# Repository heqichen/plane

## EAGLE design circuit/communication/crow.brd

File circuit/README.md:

using eagle 7.0

#ruels
1. resistor
R-US_0207/10(R-US)

2. smd resistor
R-US M0805

3. Jumper
PINHD-<num>x<num>

4. Capasitor
cpol-usud-5X5,8

5. SMA
view crow

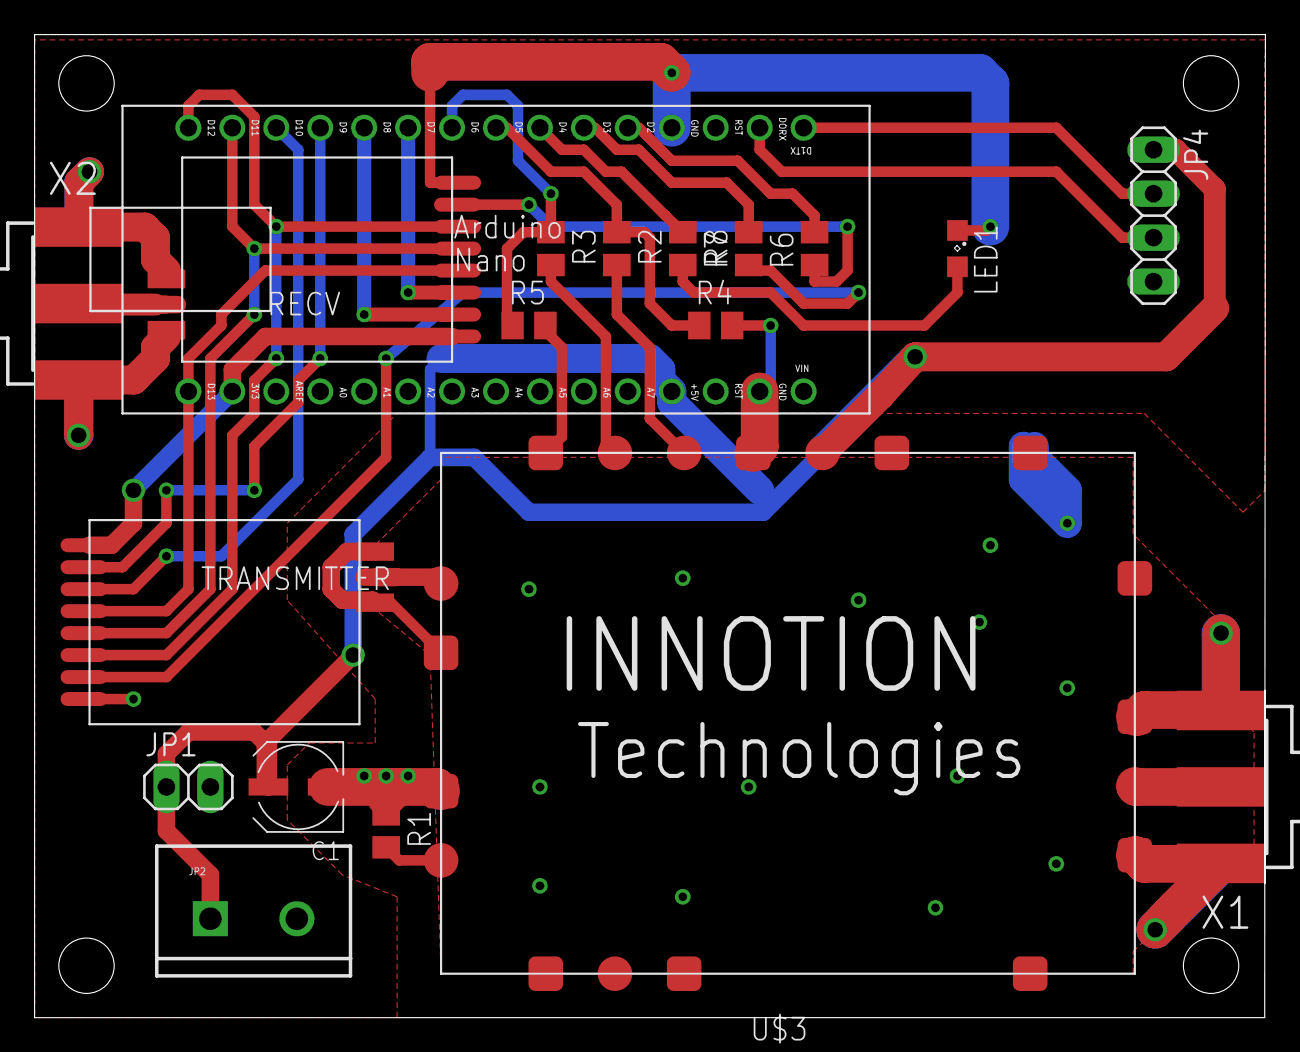
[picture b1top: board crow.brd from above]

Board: 2 copper layers, 71.1 x 56.8 mm, 19 parts (0 on the bottom side), 26 nets.

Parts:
C1: UD-5X5,8_NICHICON
JP1: 1X02
JP2: M025MM; SCREWTERMINAL-5MM-2
JP4: 1X04
LED1: SML0805
PCB1: ARDUINO_NANO_EXT; ARDUINO_NANO
R1: 50; M0805
R2, R3, R5, R6, R7, R8: 1k; M0805
R4: 10k; M0805
RECV: NRF24L01-AS01-ML01IPX; AS01-ML01IPX
TRANSMITTER: NRF24L01-AS01-ML01IPX; AS01-ML01IPX
U$3: 2.5W-TDD
X1, X2: SMA-142-0701-801/806; J502-ND-142-0701-801/806

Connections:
3V3: PCB1.3V3, RECV.3V3, TRANSMITTER.3V3
5V: C1.+, JP1.1, JP2.1, JP4.1, PCB1.5V, U$3.VPA
D2: PCB1.D2, R6.2
D3: PCB1.D3, R7.2
D5: PCB1.D5, R2.1, R4.1
D6: PCB1.D6, R3.1, R5.1
D7: PCB1.D7, RECV.CSN
D8: PCB1.D8, RECV.CE
D9: PCB1.D9, TRANSMITTER.CE
D10: PCB1.D10, TRANSMITTER.CSN
GND: C1.-, JP1.2, JP2.2, JP4.4, LED1.C, PCB1.GND, PCB1.GND., R1.1, R4.2, R5.2, RECV.GND, RECV.GND-ANT1, RECV.GND-ANT2, TRANSMITTER.GND, TRANSMITTER.GND-ANT1, TRANSMITTER.GND-ANT2, U$3.GND1, U$3.GND1-ANT, U$3.GND2, U$3.GND2-ANT, U$3.GND3, U$3.GND4, U$3.GND5, U$3.GND6, U$3.GND-RFIN, U$3.GND-RFOUT, U$3.GND-RX, U$3.GND-TX, X1.G@1, X1.G@2, X1.G@3, X1.G@4, X2.G@1, X2.G@2, X2.G@3, X2.G@4
MISO: PCB1.D12, RECV.MISO, TRANSMITTER.MISO
MOSI: PCB1.D11, RECV.MOSI, TRANSMITTER.MOSI
unnamed: R1.2, U$3.RFIN
unnamed: U$3.ANT, X1.1
unnamed: R7.1, TRANSMITTER.IRQ
unnamed: RECV.ANT, X2.1
unnamed: TRANSMITTER.ANT, U$3.RFOUT
unnamed: R6.1, RECV.IRQ
unnamed: PCB1.D4, R8.1
unnamed: LED1.A, R8.2
RX: JP4.3, PCB1.RX1
RXEN: R3.2, U$3.RX
SCK: PCB1.D13, RECV.SCK, TRANSMITTER.SCK
TX: JP4.2, PCB1.TX1
TXEN: R2.2, U$3.TX

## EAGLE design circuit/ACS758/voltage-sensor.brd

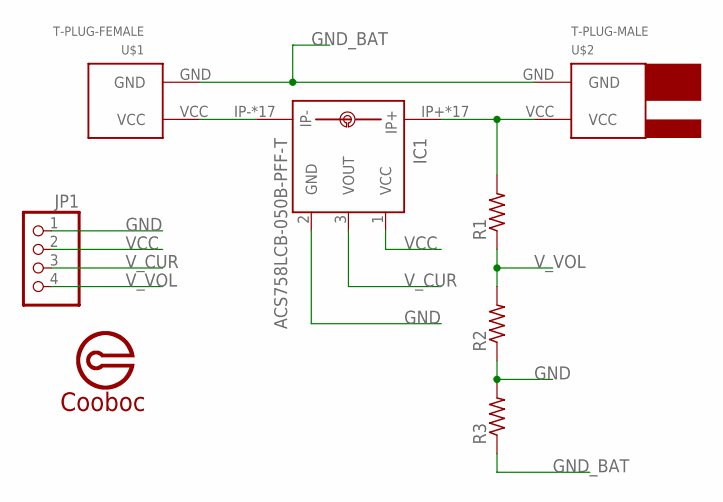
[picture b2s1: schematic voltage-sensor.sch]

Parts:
IC1: ACS758LCB-050B-PFF-T; CB-PFF
JP1: PINHD-1X4; 1X04
R1, R2: R-US_M0805; M0805
R3: R-US_0207/10; 0207/10
U$1: T-PLUG-FEMALE; T-FEMALE
U$2: T-PLUG-MALE; T-MALE
U$3: COOBOC

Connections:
GND: IC1.2 (GND), JP1.1, R2.1, R3.2; also elsewhere on the board
GND_BAT: R3.1, U$1.GND, U$2.GND
unnamed: IC1.IP-, IC1.IP-@2 (IP-), IC1.IP-@3 (IP-), IC1.IP-@4 (IP-), IC1.IP-@5 (IP-), IC1.IP-@6 (IP-), IC1.IP-@7 (IP-), IC1.IP-@8 (IP-), IC1.IP-@9 (IP-), IC1.IP-@10 (IP-), IC1.IP-@11 (IP-), IC1.IP-@12 (IP-), IC1.IP-@13 (IP-), IC1.IP-@14 (IP-), IC1.IP-@15 (IP-), IC1.IP-@16 (IP-), IC1.IP-@17 (IP-), U$1.VCC
VBAT: IC1.IP+, IC1.IP+@2 (IP+), IC1.IP+@3 (IP+), IC1.IP+@4 (IP+), IC1.IP+@5 (IP+), IC1.IP+@6 (IP+), IC1.IP+@7 (IP+), IC1.IP+@8 (IP+), IC1.IP+@9 (IP+), IC1.IP+@10 (IP+), IC1.IP+@11 (IP+), IC1.IP+@12 (IP+), IC1.IP+@13 (IP+), IC1.IP+@14 (IP+), IC1.IP+@15 (IP+), IC1.IP+@16 (IP+), IC1.IP+@17 (IP+), R1.2, U$2.VCC
VCC: IC1.1 (VCC), JP1.2; also elsewhere on the board
V_CUR: IC1.3 (VOUT), JP1.3
V_VOL: JP1.4, R1.1, R2.2

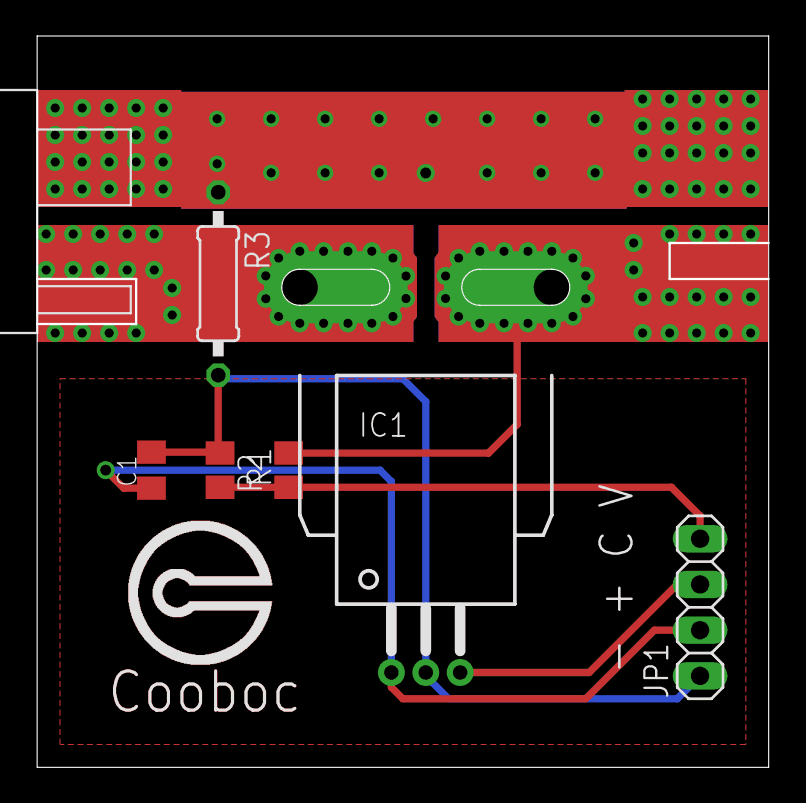
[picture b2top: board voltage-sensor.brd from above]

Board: 2 copper layers, 40.6 x 40.5 mm, 9 parts (1 on the bottom side), 7 nets.

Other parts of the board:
C1: C0805K

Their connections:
GND: C1.2; also elsewhere on the board
VCC: C1.1; also elsewhere on the board

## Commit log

2015-01-28 test arduino is good
2015-01-28 add nrf24l01 test
2015-02-16 test nrf24l01 no_ack success
2015-02-17 now can send data using nRF24l01 without ack
2015-02-17 add comment
2015-02-17 transmitter using nRF24l01 finished
2015-02-17 now can transmit data using nRF24l01
2015-02-18 change buadrate to 9600
2015-02-19 add mavlink protocol
2015-02-19 add useful nodes
2015-02-19 now can control the flight and read data from flightGear
2015-02-19 update protocol to json
2015-02-19 add gitignore file
2015-02-19 update gitignore
2015-02-19 now can read joystick value
2015-02-19 now can control flightgear with joystick
2015-02-19 add hexafsg
2015-02-20 now can show flight attitude on hexsfg
2015-02-20 update flightgear start command
2015-02-20 add makefile
2015-02-20 now can get radio
2015-02-20 add device framework
2015-02-20 add setup env script
2015-02-21 now can use radio
2015-02-21 add imu class
2015-02-21 add bmx055 driver without implementation
2015-02-21 now can start bmx055
2015-02-21 now can wakeup chicken
2015-02-21 remove chicken binary from repo
2015-02-21 now can reset acc and gyro
2015-02-21 now can read gyro data
2015-02-21 now can read acc
2015-02-21 now can running imu thread
2015-02-21 can get data from imu
2015-02-21 can send imu data via mavlink
2015-02-21 add mavlink
2015-02-22 raise update rate
2015-02-22 add auto start script
2015-02-22 add serial port -> mavlink -> flightgear test code
2015-02-23 add buzz ArduPPM
2015-02-23 pwm signal generater box finished
2015-02-23 test mavnlink generator box good
2015-02-23 now servo board can read pwm rc signal
2015-02-23 format code
2015-02-23 now can output pwm signal using rc, using Arduin Servo Library
2015-02-24 change output to simple servo output
2015-02-24 servo board can read mavlink override rc signal
2015-02-24 can send raw rc channel via serial1
2015-02-24 git remove deleted file
2015-02-24 send mavlink and write pwm in a certin routine
2015-02-24 add utp script
2015-02-24 change configuration buadrate
2015-02-24 add servo_controller
2015-02-24 reset uart to serial radio
2015-02-24 add SerialServoDriver
2015-02-24 now can read one rc channel from serial
2015-02-25 can read rc signal in chicken now
2015-02-25 now can send rc signal in driver
2015-02-25 reduce delay
2015-02-25 dummy commit
2015-02-25 nwo can override rc channel
2015-02-25 move global variable to imu member
2015-02-25 test lantcy on mega
2015-02-25 reduce servo control delay
2015-02-26 reduce servo control delay on bbb
2015-02-26 add 38400 transmitter
2015-02-26 correct folder name from dtx-38400 to dtx24-38400
2015-02-26 rename nood to node
2015-02-26 add gps test data
2015-02-27 now can read one channel data from ads7828
2015-02-27 now can read aoa and side slip
2015-02-27 add gpio library from https://github.com/mkaczanowski/BeagleBoneBlack-GPIO
2015-02-27 add files for gpio
2015-02-27 add beeper_driver files
2015-02-27 add beeper driver
2015-02-27 add beeper device
2015-02-27 beeper finished
2015-02-28 update ntp server
2015-02-28 now can read magnetometer
2015-02-28 bugfix: correct magnetometer data
2015-03-01 change beeper pin to P9_42
2015-03-01 update gpiomanager and add ultrasonic driver
2015-03-01 add ultrasonic test code on arduino
2015-03-01 bug: epoll do not work
2015-03-01 ir proximity sensor done
2015-03-02 add uav photo
2015-03-03 add test code for nrf24l01
2015-03-03 add crow communication module folder
2015-03-03 change csn pin
2015-03-03 change wide band variablewq
2015-03-03 change pvar to 24l01plus
2015-03-03 change payload size
2015-03-03 change ackpayloadAvailabe
2015-03-03 change is dynamic paload enable
2015-03-03 change ackpayloadlenght
2015-03-03 change last address set on pipe0
2015-03-03 change spi and pin
2015-03-03 update begin functionwq
2015-03-03 change writeRegister
2015-03-03 change readRegister
2015-03-03 move setPALevel
2015-03-03 update pa related code
2015-03-03 update setDataRate
2015-03-03 update setCRCLength
2015-03-03 update setDynamicPayloads
2015-03-03 update toggleFetature
2015-03-03 update flush related functions
2015-03-03 now can send and receive in full duplex
2015-03-03 complete test code for full duplex commnucatioin module
2015-03-03 add altitude fusion
2015-03-03 corrent altitude fusion to attitude indicator
2015-03-03 add virtualImu
2015-03-03 add radio fetch thread
2015-03-04 move arduino test program to arduino folder
2015-03-04 add ACS756 application image
2015-03-04 cam read attitude from flightgear and send to chicken
2015-03-04 now can read attitude from radio mavlink massage
2015-03-04 now can output virutal imu data
2015-03-04 add adi
2015-03-04 adi finished
2015-03-04 test adi
2015-03-04 output data in rad
2015-03-05 add interval thread
2015-03-05 now can decide flight status
2015-03-05 add pid files
2015-03-05 add average filter
2015-03-05 now can control elevator
2015-03-05 add servo control mode
2015-03-05 add I in pid
2015-03-05 add attitude navigator
2015-03-05 now can switch navigator
2015-03-05 add Navigator interface
2015-03-05 change manully navigator to navigator interface
2015-03-05 change all navitgator follow INavigator interface
2015-03-06 can stablize static target attitude
2015-03-06 now can stablize roll
2015-03-06 now can change attitude target in attitude navigator
2015-03-06 remove Attitude , duplicated with ImuAttitude
2015-03-06 add rudder control when bank angle
2015-03-06 now can control pitch and roll
2015-03-06 now can stablize yaw using rudder
2015-03-06 update pid parameter
2015-03-06 stalizer finished
2015-03-07 add cad file
2015-03-07 bulkhead with side holder
2015-03-07 add holes on fuselage
2015-03-07 add connector with button panel
2015-03-07 add connect between bulkhead and bottom
2015-03-07 add connector with top
2015-03-07 remove temp file
2015-03-08 bugfix: resoleve top cover conflict
2015-03-08 fuselage finished
2015-03-08 add connecting hole
2015-03-09 add cut file of 20150208
2015-03-09 vw side connect finished
2015-03-09 add hole on bulkhead
2015-03-09 add center holes on bulkhead
2015-03-09 add bottom panel
2015-03-09 change to 2mm
2015-03-09 cut this version and fix some bug
2015-03-09 add connect on top
2015-03-09 bugfix, filber tube is 16mm
2015-03-09 move hole to correct position
2015-03-09 add circuit folder
2015-03-09 add acs758
2015-03-09 update gitignore file add eagle backup file
2015-03-10 add male t plug
2015-03-10 add female t plug
2015-03-10 add some library
2015-03-10 add resistor rules
2015-03-10 update design rules
2015-03-10 sch done
2015-03-10 add eagle backup files to gitignore
2015-03-10 voltage and current sensor done
2015-03-10 layout done
2015-03-10 add capicator on asc758
2015-03-10 add arduino library from element14
2015-03-10 add top cover
2015-03-10 add back top cover
2015-03-10 add connection to kt side board
2015-03-10 add hole on back top board
2015-03-10 rm librecad backup file
2015-03-10 i don't know where changed...
2015-03-11 add 2.5w pa pinmap
2015-03-11 add size of tdd in document
2015-03-11 add 2.5w tdd layout
2015-03-11 add AS01-ML01IPX layout
2015-03-11 add nrf24l01 sch
2015-03-11 add bbb and arduino dimension
2015-03-11 add carbin for device
2015-03-12 add aluminium tube fuselage test
2015-03-12 add third version of fuselage
2015-03-12 add cut files
2015-03-12 add http framework
2015-03-14 update structrte
2015-03-14 now can show whole map
2015-03-15 enlarge hole for aluminin tube
2015-03-15 revert to v2 head
2015-03-15 add hole for connect head on bulkhead
2015-03-15 side kt connector
2015-03-15 change zoom level from 18 to 14 to show bigger map
2015-03-15 remove dummy file
2015-03-15 now can cache map
2015-03-15 now can cache map meanwhile send map
2015-03-16 now can calculate pixel around center tile
2015-03-16 now can show gps in center
2015-03-16 now can show gps on mouse pointer
2015-03-16 now can move map using right click
2015-03-19 bugfix: update serial handler, and add sa modem
2015-03-20 add gerber files
2015-03-20 add auto-run script and auto-run generate script
2015-03-21 bugfix: side slot from 1.5mm to 2.0mm and extend bottom board
2015-03-21 add side kt connectior
2015-03-22 kt connector finished
2015-03-22 bugfix: reenforcement bottom board
2015-03-22 kt and motor borad finished
2015-03-23 tail finished
2015-03-23 taile: add side holes, bugfix:add hole for servo,
2015-03-24 add smd nrf24l01 module
2015-03-24 add modules on crow
2015-03-25 crow sch done
2015-03-26 crow done, need print to check
2015-03-26 add print files
2015-03-31 add controller handler holder test board
2015-03-31 add version4 test cutting file
2015-03-31 add air foils
2015-03-31 add wing outline
2015-04-03 change some designs
2015-04-03 fix some bug and make release files
2015-04-03 add arduino test program for asc758
2015-04-03 add wing design for 12kg
2015-04-03 rm dwg file
2015-04-05 test wing for 12kg
2015-04-05 Change the side hole position, add one simple cabin design
2015-04-05 add 12kg wing test file and release files
2015-04-05 add test file for testing the crow board
2015-04-06 i don't kown...
2015-04-06 move side holes upwards
2015-04-06 enlarge the connector hole
2015-04-06 add pads
2015-04-06 add v6 and rename the typo
2015-04-06 add kt and kt connector cut file
2015-04-07 add final verison of tube
2015-04-07 generate release files of v6 create v7 fix some bugs
2015-04-07 add poly wheel
2015-04-07 now can send and receive each other
2015-04-08 data transceiver done
2015-04-08 add carbin
2015-04-10 Create gh-pages branch via GitHub
2015-04-11 add holes for mortor
2015-04-12 add debug macro to controll output from attitude_controller
2015-04-20 add tailhook
2015-04-20 update model

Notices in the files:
parts and their libraries:
SparkFun-Connectors: Licensing: Creative Commons ShareAlike 4.0 International - https://creativecommons.org/licenses/by-sa/4.0
